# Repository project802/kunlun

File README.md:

# Kunlun Keyboard Repair and Upgrade

This repository contains documentation for repairing and upgrading the Kunlun keyboard from YDKB / KBDfans.

My Kunlun stopped functioning after one too many [ESD strikes](https://en.wikipedia.org/wiki/Electrostatic_discharge) approximately 3 years into ownership. The journey to create this documentation started because I wanted to bring my keyboard back to life, and there were no replacement parts.

The failure mode presented as "ghost" key presses. Pressing one key anywhere on the PCB with the failed shift register(s) would register many or all (depending on the duration of the keypress) keys from the same PCB.

As I began the repair, I realized that the design was not something I had seen before, nor was it one commonly seen in the mechanical keyboard community (for good reason, see the section below on shift registers). It is remarkably simple, and therefore remarkably easy to diagnose and repair.

## MCU Board Redesign

I have designed a replacement MCU board based on an STM32F072. For more information, [see the mcu board redesign folder](mcu%20board%20redesign/). Improvements include ESD support, an upgraded processor that allows for enabling all Vial features, and a speaker.

## Updated Firmware for Original MCU
During this process, I also ported the [original firmware written by YDKB](https://github.com/yangdigi/vial-qmk-v5/tree/ava) to the latest version of Vial. QMK has grown a lot since Kunlun was introduced, so it required some optimization and feature set choices to be made to fit within the microcontroller constraints. 

My port can be found here: https://github.com/project802/vial-qmk

A prebuilt image can be found in the [prebuilt binaries folder](prebuilt/).

To update the firmware:

- Rename firmware image to "kunlun.bin".
- Unplug the keyboard
- Press and hold the ESC key
- Plug in keyboard
- Copy (or drag and drop) the firmware image onto the storage device presented by the keyboard

## Keyboard Design

### Major Components

**Microcontroller - Atmel Mega32U4-AU** ([datasheet](https://github.com/project802/kunlun/blob/main/spec%20sheets/Atmel-7766-8-bit-AVR-ATmega16U4-32U4_Datasheet.pdf))

A basic 8-bit microcontroller that is commonly seen in keyboards that support QMK. KBDfans used the TQFP44 package and placed it on a small PCB just for the usb interface, power supply, and microcontroller.

Kunlun uses the internal oscillator and only operates at 8 MHz, as VCC is connected to a regulated 3.3V supply and 16 MHz would require > 4.5V.

**Shift Registers - 74HC595** ([datasheet](https://github.com/project802/kunlun/blob/main/spec%20sheets/FM%2074HC595A.pdf))

When is a 74HC595 not a 74HC595? When its the one used on this keyboard. Apparently, [FM](https://www.superchip.cn/frontEn/index) decided to usurp the identifier and make something that is almost the same, but isn't. It uses open drain outputs (instead of push/pull) and also doesn't have either a latch clock nor output enable. 

The part is available on [LCSC](https://www.lcsc.com/product-detail/C110383.html).

This drove almost the entirety of why I went on the reverse engineering journey. The faulty shift registers were replaced with standard parts, and the keyboard had the same failure symptoms. After much head scratching, I figured they had to be open drain outputs and searched Google to [find a Facebook post](https://www.facebook.com/groups/955185619738067/posts/1121342913122336/) and [an EEVblog thread](https://www.eevblog.com/forum/projects/when-is-a-74hc595-not-a-74hc595/) that confirmed my suspicion. 

### Theory of Operation

The matrix is scanned entirely using only 3 GPIO. 

- PB1 - Serial data clock
- PB2 - Right PCB input, pull-up enabled
- PB3 - Left PCB input, pull-up enabled OR serial data

Serial clock and data are sent to the left and right PCB in parallel.

All switches on the right PCB have one side tied to a unique shift register output, and the other to PB2.

All switches on the left PCB have one side tied to a unique shift register output, and the other to PB3 through a 2.2kOhm resistor.

The shift registers on each PCB are run in serial so that shifting the test bit goes through each output sequentially.

Pressing a key acts as a jumper between its corresponding shift register output with the appropriate microcontroller input. If the shift register output is open drain (the bit is set to one), voltage at the microcontroller is not affected and remain logically high. If the shift register output is driven low (the keypress test bit, zero) then it will pull down the appropriate microcontroller input.

**Scanning**

- The matrix scan starts with clocking in the keypress test bit, a zero, by driving PB3 low and pulsing the PB1 data clock. PB3 is turned around to an input with pull-up.
- Both PB2 and PB3 inputs are evaluated for a keypress.
- The keypress test bit is shifted down one position in the shift register banks by driving PB3 high, pulsing the PB1 clock, then turning PB3 back to an input with pull-up.
- The loop of evaluate and shift continues until all register outputs have been scanned: the greater of the left (32) and right (40) outputs is 40 iterations.

That's it. It is arguably slower than a typical row/col matrix, but it can still be completed in short order (optimized to approximately 350 microseconds in my port) so it doesn't present any meaningful lag as the USB HID interface runs on a 1 millisecond interval. As a result, the stock and ported firmware restrict the scan rate to no faster than 1 kHz.

## Diagnosing a failed board

The photos in this section display the behavior of stock firmware. My ported firmware has different waveforms and sequences.

In my case, the microcontroller appeared to have full function so my focus was on the left and right PCBs. 

The right PCB was the closest to where the final ESD strike occurred so that is also where I started checking. There was no visible physical damage, so the first tests were to probe the various pins on the shift registers.

Starting with the first register in the chain, U24, verify inputs on pins 11 (clock) and 14 (data). You should see something similar to below.

The data (yellow trace) can be seen driving low, clocked in, and slowly rising due to the weak pull-up.

Next, check pin 9 to make sure the IC is shifting the bit out and into the next one in the chain. In my case, this was part of the failure mode. It was not outputting anything but low so it was clocking in zeros to the next IC, so on and so forth, causing everything to look like it was pressed at the same time. 

Check the outputs of the shift register to make sure they are switching between open drain and driving low. You will need to press a key to connect the output to the pull-up within the micro, otherwise it will look like its driving low the entire time. It isn't! I also had this failure mode where the lines were driving low. It seems my IC had a dead data input internally and was always reading zeros so it latched those to the outputs and shifted it into the next in line.

A key pressed with its shift register output (yellow) and the bit clock (blue) is below.

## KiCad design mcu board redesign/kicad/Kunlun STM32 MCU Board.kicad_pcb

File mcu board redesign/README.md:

# Kunlun MCU Board Redesign

This is a redesign of the MCU board in the KBDFans Kunlun keyboard with the primary purpose of switching to an STM32F072 processor. The stock ATMega-based design is great, but the part is limited in code space and EEPROM to enable all of the modern Vial features. 

Improvements over the stock design:
* STM32F072 to enable all current Vial features
* Piezo speaker/buzzer
* ESD protection on USB
* Chassis grounding with ESD protection and static buildup mitigation

Otherwise, it reuses the same board geometry, mounting features, and connector locations as stock.

The pug is Moose. He was a good boy.

## Vial Support
### Prebuilt
A prebuilt binary can be found in the prebuilt folder: https://github.com/project802/kunlun/tree/main/prebuilt 

### Build from source
Download my fork of Vial here: https://github.com/project802/vial-qmk

Follow the normal Vial setup instructions. Build the binary with the command below:

        make project802/kunlun:vial

### Flashing
Flash as usual using the STM32 DFU mode.

## Design Files and BOM

Design files were made with KiCad 10. Full schematic and PCB are included.

The BOM is included in the [KiCad design files](kicad/), and as an export in the [production folder](kicad/production/). The export was done with JLCPCB's fabrication output plugin as I primarily use them as my fab house.

[Web-based interactive BOM and layout](https://htmlpreview.github.io/?https://github.com/project802/kunlun/blob/main/mcu%20board%20redesign/kicad/bom/ibom.html) 

[Digikey Full BOM](https://www.digikey.com/en/mylists/list/4LIAA4M82M) - All components including debug features (~$15 USD) 

[Digikey Minimal BOM](https://www.digikey.com/en/mylists/list/V16MMQCCVU) - No debug features and no speaker (~$11 USD)

At the time of writing (5/2026), the cost for 5 boards with a nano coated and electropolished stencil to the US from JLCPCB was $21 USD. Boards alone are $5-$6 shipped.

### Manufacturing Data
FR4, 2 layers, 1.6mm thick, 1 oz copper

PCB Color: white with black silkscreen

## Pinout

*Functional Pins*

| Pin | Function |
|:---:|:---------|
| PA0 | Matrix data / Left PCB input |
| PA1 | Matrix clock |
| PA2 | Right PCB input |
| PA3 | WS2812 LED data |
| PA8 | Speaker output |

*Optional / Debug Pins*

| Pin | Function |
|:---:|:---------|
| PA13 | SWDIO |
| PA14 | SWCLK |
| PB3  | DEBUG_GPIO |
| PB6  | USART1_TX |
| PB7  | USART1_RX |
| PB15 | Speaker Alt (differential drive) |

*Debug Header*

| Pin | Function |
|:-:|:---------|
| 1 | USART1_RX |
| 2 | NRST |
| 3 | DEBUG_GPIO |
| 4 | USART1_TX |
| 5 | VDD (3.3V) |
| 6 | SWCLK |
| 7 | SWDIO |
| 8 | VSS (GND) |

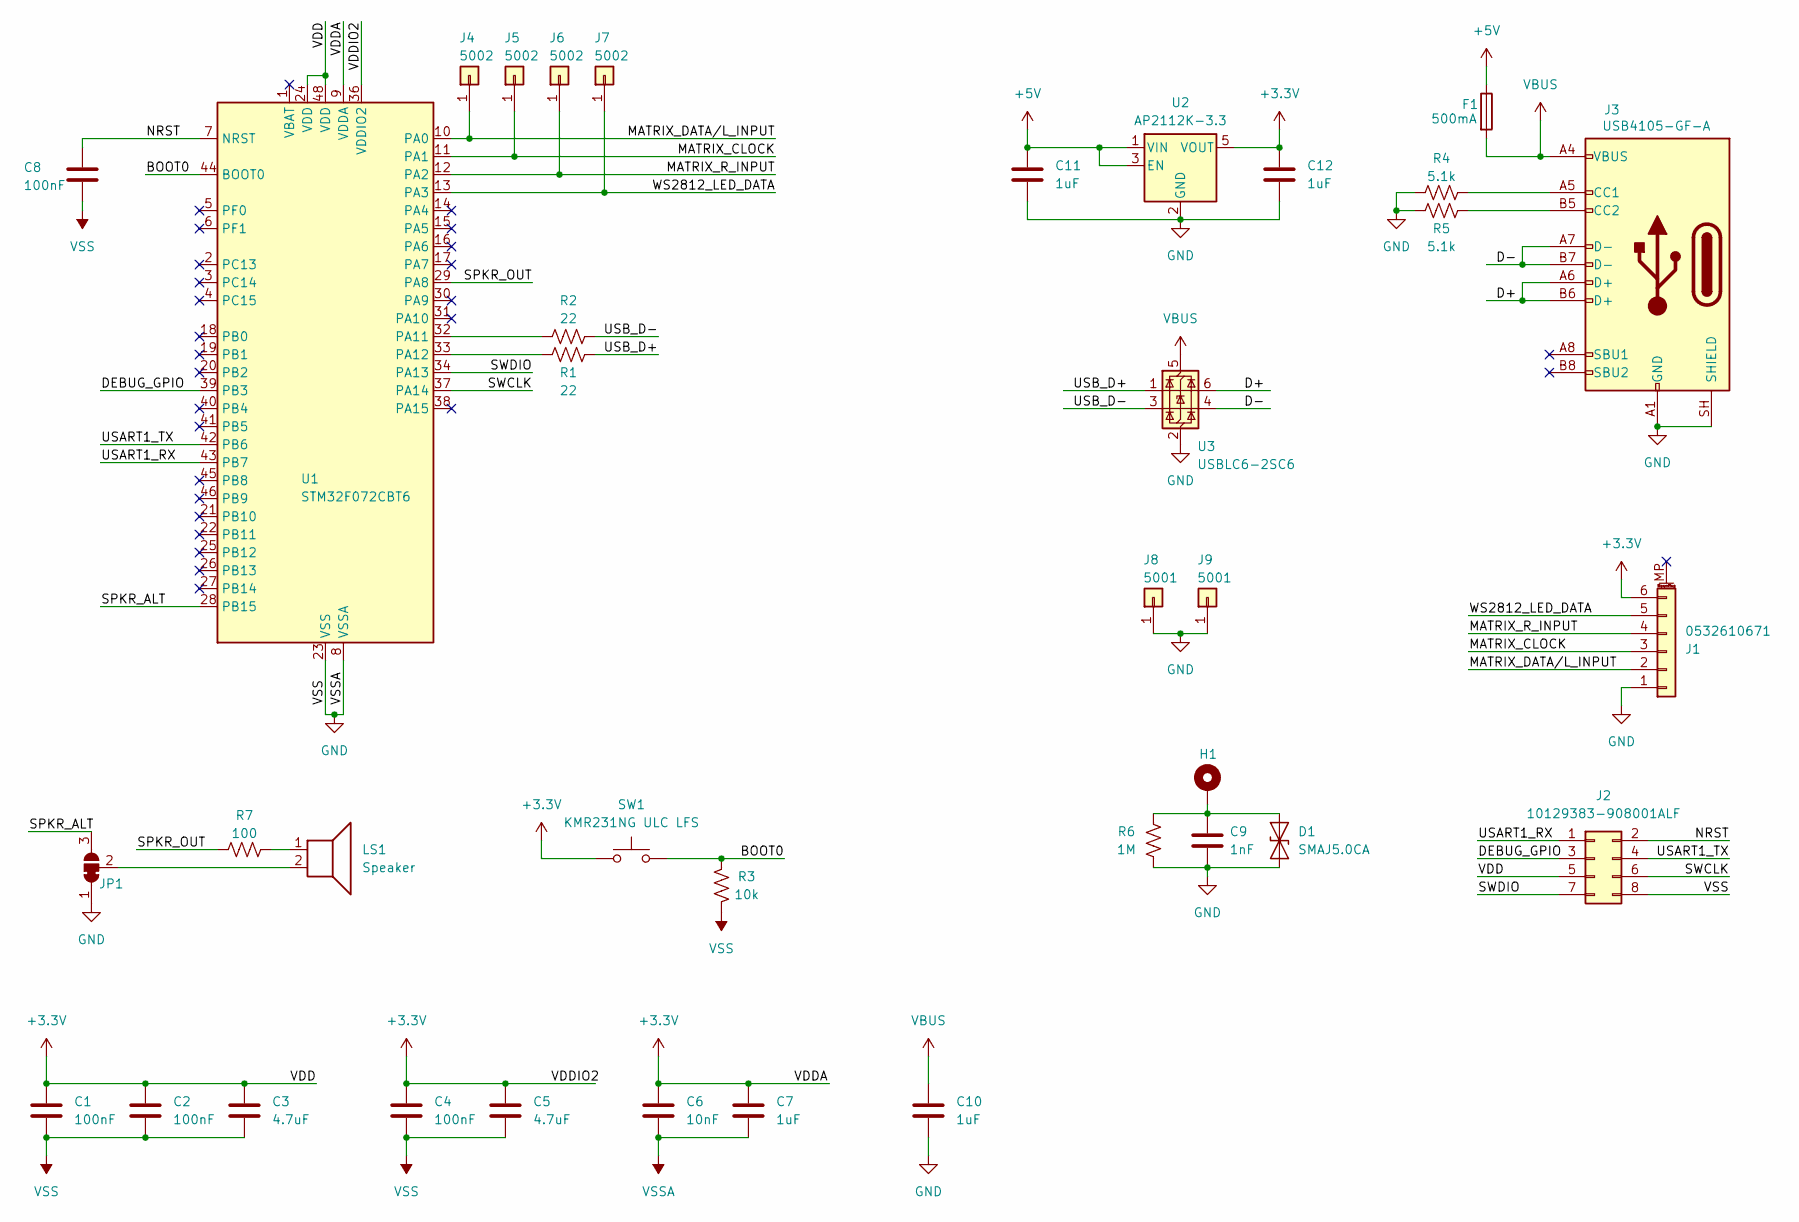
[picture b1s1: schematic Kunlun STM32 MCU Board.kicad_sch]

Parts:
C1, C2, C4, C8: 100nF; C_0603_1608Metric; Digikey 399-C0603C104K5RACTUCT-ND
C3, C5: 4.7uF; C_0603_1608Metric; Digikey 1276-2087-1-ND
C6: 10nF; C_0603_1608Metric; Digikey 399-C0603C103K5RACTUCT-ND
C7, C10, C11, C12: 1uF; C_0603_1608Metric; Digikey 399-C0603C105K4RACTUCT-ND
C9: 1nF; C_1206_3216Metric; Digikey 311-1489-1-ND
D1: SMAJ5.0CA; D_SMA; Digikey SMAJ5.0CALFCT-ND
F1: 500mA; Fuse_1206_3216Metric; Digikey 5923-0ZCJ0050FF2GCT-ND
H1: MountingHole_Pad; MountingHole_2.2mm_M2_Pad
J1: 0532610671; Molex_PicoBlade_53261-0671_1x06-1MP_P1.25mm_Horizontal; Digikey WM7624CT-ND
J2: 10129383-908001ALF; PinHeader_2x04_P2.54mm_Vertical_SMD; Digikey 609-10129383-908001ALFCT-ND
J3: USB4105-GF-A; USB_C_Receptacle_GCT_USB4105-xx-A_16P_TopMnt_Horizontal; Digikey 2073-USB4105-GF-ACT-ND
J4, J5, J6, J7: 5002; TestPoint_Keystone_5000-5004_Miniature; Digikey 36-5002-ND
J8, J9: 5001; TestPoint_Keystone_5000-5004_Miniature; Digikey 36-5001-ND
JP1: SolderJumper_3_Bridged12; SolderJumper-3_P1.3mm_Bridged12_RoundedPad1.0x1.5mm
LS1: Speaker; Buzzer_CUI_CPT-9019S-SMT; Digikey 102-3761-1-ND
R1, R2: 22; R_0603_1608Metric; Digikey RMCF0603FT22R0CT-ND
R3: 10k; R_0603_1608Metric; Digikey RMCF0603JT10K0CT-ND
R4, R5: 5.1k; R_0603_1608Metric; Digikey RMCF0603FT5K10CT-ND
R6: 1M; R_1206_3216Metric; Digikey RMCF1206FT1M00CT-ND
R7: 100; R_0603_1608Metric; Digikey RMCF0603FT100RCT-ND
SW1: KMR231NG ULC LFS; SW_Push_1P1T_NO_CK_KMR2; Digikey CKN10284CT-ND
U1: STM32F072CBT6; LQFP-48_7x7mm_P0.5mm; Digikey 497-14645-ND
U2: AP2112K-3.3; SOT-23-5; Digikey AP2112K-3.3TRG1DICT-ND
U3: USBLC6-2SC6; SOT-23-6; Digikey 497-5235-1-ND

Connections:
+3.3V: C1.1, C2.1, C3.1, C4.1, C5.1, C6.1, C7.1, C12.1, J1.6, J2.5, SW1.1, U1.9 (VDDA), U1.24 (VDD), U1.36 (VDDIO2), U1.48 (VDD), U2.5 (VOUT)
+5V: C11.1, F1.1, U2.1 (VIN), U2.3 (EN)
/BOOT0: R3.1, SW1.2, U1.44 (BOOT0)
/D+: J3.A6 (D+), J3.B6 (D+), U3.6 (I/O1)
/D-: J3.A7 (D-), J3.B7 (D-), U3.4 (I/O2)
/DEBUG_GPIO: J2.3, U1.39 (PB3)
/MATRIX_CLOCK: J1.3, J5.1 (Pin_1_1), U1.11 (PA1)
/MATRIX_DATA/L_INPUT: J1.2, J4.1 (Pin_1_1), U1.10 (PA0)
/MATRIX_R_INPUT: J1.4, J6.1 (Pin_1_1), U1.12 (PA2)
/NRST: C8.1, J2.2, U1.7 (NRST)
/SPKR_ALT: JP1.3 (B), U1.28 (PB15)
/SPKR_OUT: R7.2, U1.29 (PA8)
/SWCLK: J2.6, U1.37 (PA14)
/SWDIO: J2.7, U1.34 (PA13)
/USART1_RX: J2.1, U1.43 (PB7)
/USART1_TX: J2.4, U1.42 (PB6)
/USB_D+: R1.1, U3.1 (I/O1)
/USB_D-: R2.1, U3.3 (I/O2)
/WS2812_LED_DATA: J1.5, J7.1 (Pin_1_1), U1.13 (PA3)
GND: C1.2, C2.2, C3.2, C4.2, C5.2, C6.2, C7.2, C8.2, C9.2, C10.2, C11.2, C12.2, D1.1 (A1), J1.1, J2.8, J3.A1 (GND), J3.A12 (GND), J3.B1 (GND), J3.B12 (GND), J3.SH (SHIELD), J8.1 (Pin_1_1), J9.1 (Pin_1_1), JP1.1 (A), R3.2, R4.2, R5.1, R6.2, U1.8 (VSSA), U1.23 (VSS), U1.35 (VSS), U1.47 (VSS), U2.2 (GND), U3.2 (GND)
unnamed: C9.1, D1.2 (A2), H1.1 (1_1), R6.1
unnamed: J3.A5 (CC1), R4.1
unnamed: J3.B5 (CC2), R5.2
unnamed: JP1.2 (C), LS1.2
unnamed: LS1.1, R7.1
unnamed: R2.2, U1.32 (PA11)
unnamed: R1.2, U1.33 (PA12)
VBUS: C10.1, F1.2, J3.A4 (VBUS), J3.A9 (VBUS), J3.B4 (VBUS), J3.B9 (VBUS), U3.5 (VBUS)

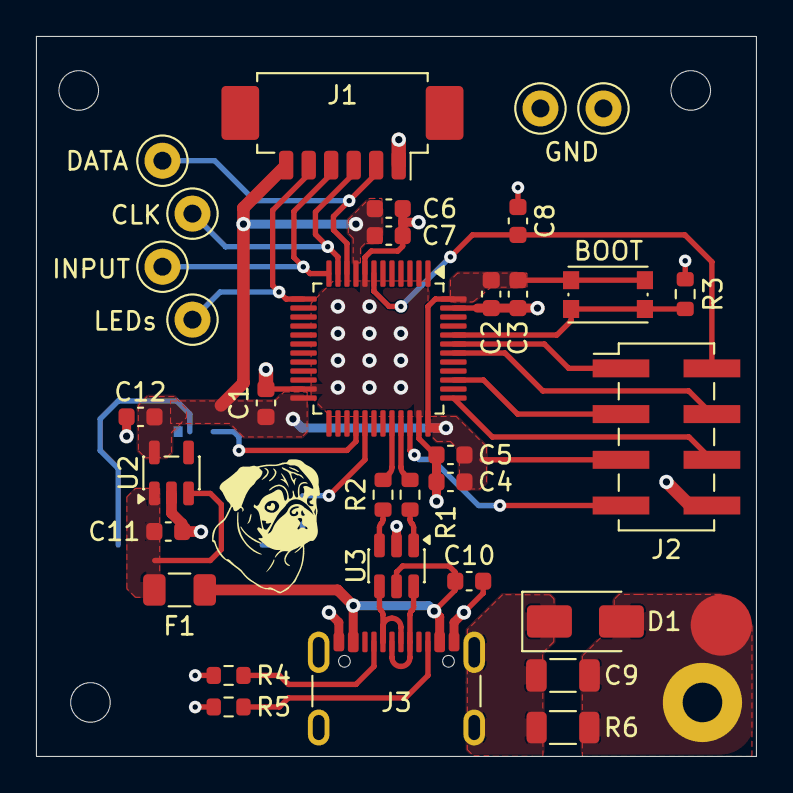
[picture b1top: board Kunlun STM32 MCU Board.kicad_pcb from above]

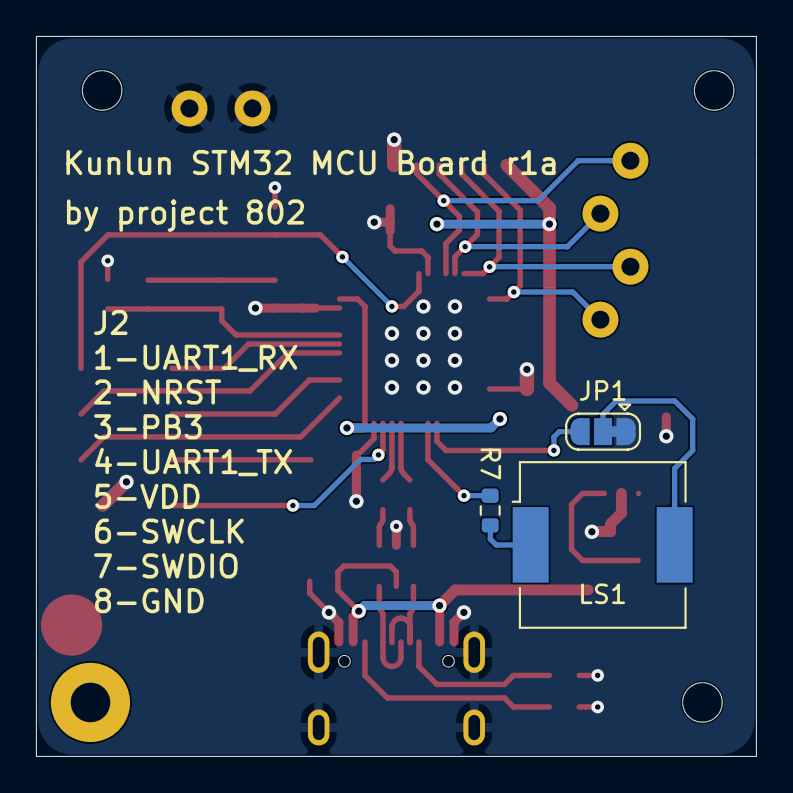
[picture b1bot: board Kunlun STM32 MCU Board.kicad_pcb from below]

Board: 2 copper layers, 40.0 x 40.0 mm, 37 parts (3 on the bottom side), 28 nets.

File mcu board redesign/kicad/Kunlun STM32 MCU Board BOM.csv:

"Reference","Qty","Value","PartNo"
"C1,C2,C4,C8","4","100nF","399-C0603C104K5RACTUCT-ND"
"C3,C5","2","4.7uF","399-C0603C475K9PACTUCT-ND"
"C6","1","10nF","399-C0603C103K5RACTUCT-ND"
"C7,C10,C11","3","1uF","399-C0603C105K4RACTUCT-ND"
"C9","1","1nF","311-1489-1-ND"
"F1","1","500mA","MF-MSMF050-2CT-ND"
"J1","1","0532610671","WM7624CT-ND"
"J2","1","10129383-908001ALF","609-10129383-908001ALFCT-ND"
"J3","1","USB4105-GF-A","2073-USB4105-GF-ACT-ND"
"J4,J5,J6,J7","4","5002","36-5002-ND"
"J8,J9","2","5001","36-5001-ND"
"R1,R2","2","22","RMCF0603FT22R0CT-ND"
"R3","1","10k","RMCF0603JT10K0CT-ND"
"R4,R5","2","5.1k","RMCF0603FT5K10CT-ND"
"R6","1","1M","RMCF1206FT1M00CT-ND"
"SW1","1","KMR231NG ULC LFS","CKN10284CT-ND"
"U1","1","STM32F072CBT6","497-14645-ND"
"U2","1","AP2112K-3.3","AP2112K-3.3TRG1DICT-ND"
"U3","1","USBLC6-2SC6","497-5235-1-ND"

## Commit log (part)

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2026-05-08 Fix image urls and some wording.
2026-05-13 Initial MCU redesign commit
2026-05-15 Lots of updates
    Add ESD protection R6/C9
    Layout changes for bypass caps
    Layout changes to pass all JLC DFM checks
    Fill out J2 and optimize routing
2026-05-15 Ignore a few more things
2026-05-15 Initial BOM
2026-05-16 Mostly layout updates
    Add VBUS decoupling cap.
    Rearrange traces for less ground plane chops and fewer vias.
    Move some components around for trace optimization (boot switch, etc)
    Tweak the decoupling caps
    Remove pads from 3 mounting holes to avoid potential chassis ground loops
2026-05-16 Make D- pretty at the connector
2026-05-16 More pretty things
    Curve the fill around chassis ground mounting hole.
    Label switch as "BOOT"
    Pretty up R4
    Small trace tweaks
2026-05-16 Pretty up traces to J1
2026-05-16 Fatten up NRST going to the pin on U1
2026-05-16 Added speaker, changed fuse.
2026-05-16 Slide power section closer to MCU
    And associated layout tweaks
2026-05-16 Set correct PartNo for R7
2026-05-20 Add a TVS to ESD circuit
2026-05-22 Add LCSC part numbers
2026-05-22 Updates after JLCPCB fab tools generation
2026-05-22 Update part numbers
    Found alternates in LCSC that are "basic" instead of "extended" so manufacturing is considerably less expensive (saved $30 in setup costs).
    Digikey is out of the AP2112 so list the AP7365 as an alternate.
2026-05-29 Move one trace a bit for cosmetics
2026-05-29 Move D1, C9, R4/5/6 for JLCPCB DFM
2026-05-29 First production order (PCB and stencil only, no assembly)
2026-05-30 Add README.md
2026-05-30 Add prebuilt binary for Kunlun stock MCU board
2026-06-14 Fix rear mounting hole locations
2026-06-28 Set rev to 1a
    It was set to 2 but there were other changes planned that I didn't keep.
2026-06-28 Compatible with rev 1 and 1a
    Full user functionality enabled and tested for a couple of weeks. Looks good.
2026-06-28 Enhance README with Vial support instructions
    Added instructions for prebuilt binaries and building from source for Vial support.
2026-06-28 Updated to reflect rev 1a
2026-06-28 Update README with manufacturing data and cost details
    Added manufacturing data and updated cost details for boards.
